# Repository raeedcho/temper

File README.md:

# temper

This is a split, wireless-only mechanical keyboard fashioned after the [chocofi keyboard](https://github.com/pashutk/chocofi). It started as a simple modification of the original chocofi PCBs to include battery pads and power switches for wireless use, but in the end, I thought there were enough changes to warrant giving it a separate designation. However, this design remains compatible with chocofi cases and plates.

## Features

- 36-key split keyboard with 3 rows x 5 columns + 3 thumb keys per half 
- Kailh choc spacing
- Sweep-like column stagger (with pinky columns 2 mm lower, like chocofi) with Corne-like thumb cluster
- Reversible PCB (so one design can be used for both halves)
- Kailh choc hotswap sockets
- Intended to be used with [nice!nano](https://nicekeyboards.com/nice-nano)
- Uses 7-pin SPDT power switch and includes pads for battery on keyboard shield PCB
- Support for [nice!view](https://nicekeyboards.com/nice-view)
- Compatible with chocofi cases and plates

## List of changes from original chocofi

- Add power switch
- Add solder pads for battery under ProMicro footprint
- Add footprint for a nice!view screen
- Switch out diode footprints for ones that have solder pads on both sides
- Switch ProMicro footprint for one that uses solder jumpers for cleaner design
- Remove TRRS jack
- Change reset switch out for one I could easily source from [Typeractive](https://www.typeractive.xyz)
- Rework KiCAD schematic for more pleasant development

## Bill of Materials

- 2x PCB (gerber files in [releases](https://github.com/raeedcho/temper/releases))
- 2x nice!nanos
- 2x LiPo batteries (see nice!nano documentation for suggestions)
- 2x Alps miniature SPDT switches
- 2x Panasonic miniature momentary button switches 
- 36x Kailh choc v1 switches
- 36x Kailh choc hotswap sockets
- 36x Choc v1 keycaps
- 36x 1N4148W SMD diodes
- (Technically optional but highly recommended) MCU socket:
  - 4x Mill-Max 310 series machine sockets
  - 48x Mill-Max pins for socketing microcontrollers
- (Optional) Minimal back plate case:
  - 2x 3mm acrylic back plate (SVG file for laser cutting in [case folder](case/temper-bottomplate.svg))
  - 10x M2 4 or 5mm brass standoffs (I used 5mm, but some users have said that 4mm fits better)
  - 20x M2 3mm screws
- (Optional) 2x FR-4 switch plate (goes well with the back plate--gerber files in [releases](https://github.com/raeedcho/temper/releases))
- (Optional) 2x nice!view screens

## Assembly

Assembly of this keyboard requires soldering the jumpers on the front-side of each PCB (underneath the microcontrollers). Past this, the assembly of this keyboard is similar to that of many other split wireless keyboards--there are many guides online to help. In case it helps with assembly, there's a screenshot of the PCB schematic in the somewhat incomplete [PCB folder readme](https://github.com/raeedcho/temper/tree/main/pcb).

Briefly, the full list of steps includes:

- Solder the jumpers underneath where the microcontrollers and battery would go (on PCB front). It's best to do this step first, since it's easiest when there are no other components on the board.

- On PCB back:
  - Solder the diodes (ensuring diodes are oriented correctly--check diode schematic to match orientation to PCB)
  - Solder the switch sockets
- On PCB front:
  - Solder reset switch
  - Solder power switch
  - [Socket microcontroller](https://docs.splitkb.com/hc/en-us/articles/360011263059-How-do-I-socket-a-microcontroller-):
    - Solder sockets into PCB
    - Place masking tape (to divert solder from socket for next soldering step)
    - Insert Mill-Max pins or diode legs
    - Place microcontroller (blank side up)
    - Solder pins to microcontroller
    - Carefully remove microcontroller
    - Remove tape
  - (optional) socket nice!view displays (same procedure as socketing microcontroller)
  - *Carefully* solder battery wires to pads (ensuring wires don't short together--I used masking tape to secure wires)
  - Reseat microcontroller
- Putting it all together (follow specific case instructions if applicable)
  - (optional) For back plate:
    - attach standoffs to PCB with screws
    - slide PCB standoffs into the aligned backplate holes
    - secure backplate in place with M2 screws (the backplate will be sandwiched in place between the hot swap sockets and the screw heads)
  - If not using switch plate:
    - press switches directly into PCB sockets (ensuring switch legs make it into the sockets and don't bend out of the way)
  - If using switch plate:
    - press switches into plate
    - align switches with PCB holes and press into sockets (ensuring legs make it into sockets and don't bend out of the way)
  - Place keycaps on switches

## Firmware

This keyboard uses [ZMK firmware](https://zmk.dev), which allows for configuration through GitHub Actions. An example configuration repository is [here](https://github.com/raeedcho/temper-zmk-config.git). The temper has also been added as an outboard on [Miryoku ZMK](https://github.com/manna-harbour/miryoku_zmk) via this [pull request](https://github.com/manna-harbour/miryoku_zmk/pull/42).

## Case options

The temper should be compatible with any case that works on the chocofi. The pictures above show a minimal case using only a laser-cut acrylic backplate (SVG design [here](case/temper-bottomplate.svg)), held on by M2 screws and brass standoffs. It's also possible to add an FR-4 switch plate (KiCAD design [here](case/top-plate)), which helps keep the switches stable in the hot-swap sockets.

Other options:
- The [temper gasket case](https://github.com/calerouxz/TemperKB-case), designed specifically for the temper by [calerouxz](https://github.com/calerouxz). The gasket case is more complex than the simple acrylic backplate and FR-4 switch plate, but has a more polished final look and feel.
- This [custom temper case](https://github.com/AdrianBonpin/zmk-temper), designed by [AdrianBonpin](https://github.com/AdrianBonpin). This repository also contains another example firmware configuration, with support for [ZMK Studio](https://zmk.dev/docs/features/studio).
- A [CNC metal case](https://github.com/CoenTurk/temper-metal), designed by [CoenTurk](https://github.com/CoenTurk). See https://github.com/raeedcho/temper/pull/18 for images.
- A [case with room for a big 600 mAh battery](https://github.com/vdztvboven-cpu/temper-case), designed by [kulderzipke](https://github.com/vdztvboven-cpu).

## Why "temper"?

Tempering is a finicky process that changes the structure of chocolate to make it more shiny, but doesn't really change the taste much.

Likewise, the changes I made to the chocofi didn't alter the original design much, but made some quality-of-life improvements for both development and my own personal aesthetics, at the cost of removing traditional wired operation and possibly making it more difficult to assemble, given the addition of many solder jumpers. 

## Resources

I adapted a few of the elements from these KiCAD libraries for use in this design:

- [chocofi](https://github.com/pashutk/chocofi) - The PCB switch layout came from the original chocofi design
- [kbd](https://github.com/foostan/kbd) - This library, by foostan, the designer of the popular Corne keyboard, provides useful schematic symbols and footprints
- [keyswitches.pretty](https://github.com/daprice/keyswitches.pretty) - library of switch footprints--especially useful for reversible PCBs.
- [swoop](https://github.com/jimmerricks/swoop) - Contains reversible PCB footprints for ProMicro pinout, OLED screens, and 7-pin power switches.

## Similar keyboards

There are many similar keyboards to this one and the chocofi, and I'm sure they've all taken inspiration from each other at one point or another. Here's a (surely incomplete) list:

- [Corne/crkbd](https://github.com/foostan/crkbd) - A popular column stagger, 42-key split keyboard with many variants
- [Cornish Zen](https://lowprokb.ca/collections/keyboards/products/corne-ish-zen) - A low-profile wireless redesign of the Corne with choc spacing, screens, and an aluminum case
- [Kyria](https://splitkb.com/collections/keyboard-kits/products/kyria-rev3-pcb-kit) - Another popular columns stagger, 50-key split keyboard, supporting rotary encoders. MX spacing only, but supports both MX and choc switches. More extreme column stagger on the pinky than the Corne. Large thumb cluster.
- [Ferris](https://github.com/pierrechevalier83/ferris) - Minimalistic 34-key split keyboard borrowing the pinky column stagger of the Kyria. MCU is soldered directly onto the board--not ProMicro pinout compatible.
- [Ferris Sweep](https://github.com/davidphilipbarr/Sweep) - Redesign of the Ferris for ProMicro MCU pinout, which also allows for a diodeless build. Many variations.
- [Swoop](https://github.com/jimmerricks/swoop) - Fork of the Ferris Sweep to add OLED screens and encoders
- [Urchin](https://github.com/duckyb/urchin) - Another fork of the Ferris Sweep to add support for nice!view screens, though with a traditional switch matrix and diodes.
- [Swept Corne](https://github.com/AYM1607/swept-crkbd) - A wireless-only mix between the Corne and Ferris Sweep--basically a choc-spaced Corne with the Kyria pinky stagger (or alternatively a choc-spaced Kyria with a Corne thumb cluster)
- [Phase](https://github.com/mjpauly/phase) - 42-key split keyboard--mix of the original Ferris and Corne.
- [Fifi](https://github.com/raychengy/fifi_split_keeb) - 36-key split keyboard. Basically an MX Ferris Sweep with a Corne thumb cluster
- [Chocofi](https://github.com/pashutk/chocofi) - Choc version of the Fifi. Stagger is like the Kyria and Ferris keyboards, but with the pinky column 2mm lower. The keyboard this repository was based on.
- [Roost](https://github.com/forrestbaer/roost) - Wireless-only Ferris Sweep with an extra thumb key per hand
- [TOTEM](https://github.com/GEIGEIGEIST/TOTEM) - 38 key split keyboard with Sweep-like column stagger. 3 thumb keys, like Corne, but also an extra pinky key. Also designed with finger splay for the ring and pinky fingers.
- [A. Dux](https://github.com/tapioki/cephalopoda/tree/main/Architeuthis%20dux) - 34-key split keyboard with aggressive column stagger and splay
- [KLOR](https://github.com/GEIGEIGEIST/KLOR) - Customizable split keyboard (via versatile break-off PCBs), with on-board MCU, encoders, and OLED screens

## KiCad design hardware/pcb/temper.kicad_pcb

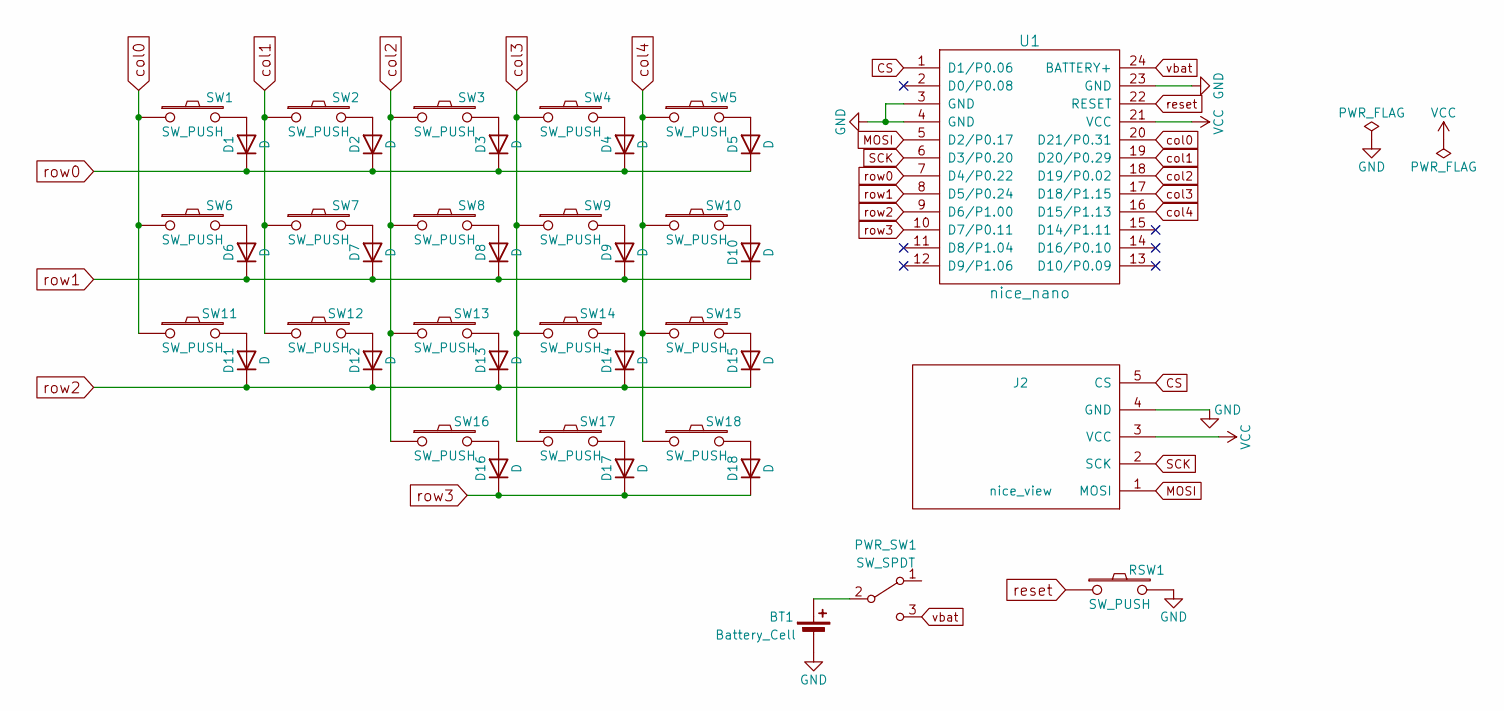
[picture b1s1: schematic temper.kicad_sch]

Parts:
BT1: Battery_Cell; Battery_pads_reversible
D1, D2, D3, D4, D5, D6, D7, D8, D9, D10, D11, D12, D13, D14, D15, D16, D17, D18: D; D_SMD_TH
J2: nice_view; nice_view_jumpers
PWR_SW1: SW_SPDT; power_switch_padreverse
RSW1: SW_PUSH; Panasonic_EVQPUL_EVQPUC_reversible
SW1, SW2, SW3, SW4, SW5, SW6, SW7, SW8, SW9, SW10, SW11, SW12, SW13, SW14, SW15, SW16, SW17, SW18: SW_PUSH; Kailh_socket_PG1350_reversible
U1: nice_nano; ProMicro_jumpers

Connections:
CS: J2.5 (CS), U1.1 (D1/P0.06)
GND: BT1.2 (-), J2.4 (GND), RSW1.2, U1.3 (GND), U1.4 (GND), U1.23 (GND)
MOSI: J2.1 (MOSI), U1.5 (D2/P0.17)
unnamed: BT1.1 (+), PWR_SW1.2 (B)
unnamed: D1.2 (A), SW1.2
unnamed: D2.2 (A), SW2.2
unnamed: D3.2 (A), SW3.2
unnamed: D4.2 (A), SW4.2
unnamed: D5.2 (A), SW5.2
unnamed: D6.2 (A), SW6.2
unnamed: D7.2 (A), SW7.2
unnamed: D8.2 (A), SW8.2
unnamed: D9.2 (A), SW9.2
unnamed: D10.2 (A), SW10.2
unnamed: D11.2 (A), SW11.2
unnamed: D12.2 (A), SW12.2
unnamed: D13.2 (A), SW13.2
unnamed: D14.2 (A), SW14.2
unnamed: D15.2 (A), SW15.2
unnamed: D16.2 (A), SW16.2
unnamed: D17.2 (A), SW17.2
unnamed: D18.2 (A), SW18.2
SCK: J2.2 (SCK), U1.6 (D3/P0.20)
VCC: J2.3 (VCC), U1.21 (VCC)
col0: SW1.1, SW6.1, SW11.1, U1.20 (D21/P0.31)
col1: SW2.1, SW7.1, SW12.1, U1.19 (D20/P0.29)
col2: SW3.1, SW8.1, SW13.1, SW16.1, U1.18 (D19/P0.02)
col3: SW4.1, SW9.1, SW14.1, SW17.1, U1.17 (D18/P1.15)
col4: SW5.1, SW10.1, SW15.1, SW18.1, U1.16 (D15/P1.13)
reset: RSW1.1, U1.22 (RESET)
row0: D1.1 (K), D2.1 (K), D3.1 (K), D4.1 (K), D5.1 (K), U1.7 (D4/P0.22)
row1: D6.1 (K), D7.1 (K), D8.1 (K), D9.1 (K), D10.1 (K), U1.8 (D5/P0.24)
row2: D11.1 (K), D12.1 (K), D13.1 (K), D14.1 (K), D15.1 (K), U1.9 (D6/P1.00)
row3: D16.1 (K), D17.1 (K), D18.1 (K), U1.10 (D7/P0.11)
vbat: PWR_SW1.3 (C), U1.24 (BATTERY+)

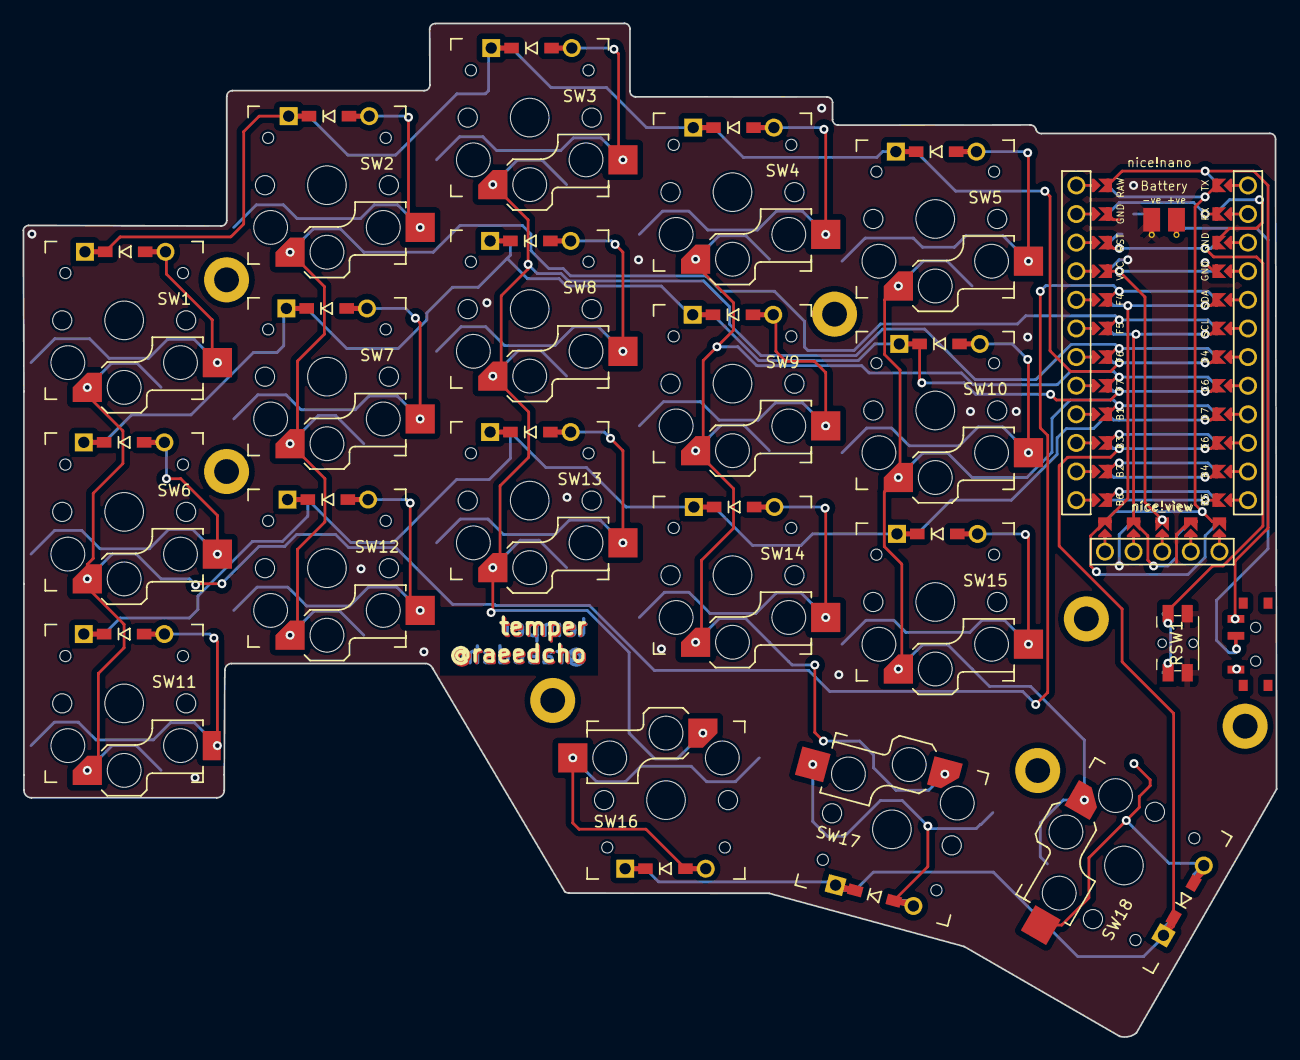
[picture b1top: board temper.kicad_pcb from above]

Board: 2 copper layers, 111.3 x 90.0 mm, 48 parts (0 on the bottom side), 35 nets.

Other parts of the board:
H1: h1; LEGO_HOLE
h2: h2; LEGO_HOLE
h3: h3; LEGO_HOLE
h4: h4; LEGO_HOLE
h5: h5; LEGO_HOLE
h6: h6; LEGO_HOLE
h7: h7; LEGO_HOLE

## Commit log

2023-07-07 feat: add gitignore
2023-07-07 feat: add kicad-specific gitignore
2023-07-07 feat: add kbd and keyswitches pcb libraries as submodules
2023-07-13 feat: add swoop footprint library
2023-07-13 feat: add specialized library for dumta keyboard
2023-07-13 feat: add dumta schematic, pcb, and other files
2023-07-13 feat: add JLCPCB design rules, as best I can tell
2023-07-13 feat: move some footprints over to dumta library
2023-07-13 feat: change footprints and alter them to match design rules
2023-07-13 fix: fix all major design rule errors
2023-07-13 chore: change design rule warning spec
2023-07-14 refactor: rename kicad project to temper, keeping the library name the same
2023-07-14 feat: change some output settings
2023-07-14 doc: add readme file
2023-07-14 Add CERN Open Hardware License
2023-07-14 fix: add nice!nano and nice!view silkscreen
2023-07-17 doc: add some info to readme
2023-07-17 doc: clean up readme a little bit
2023-08-25 doc: update readme with firmware info
2023-08-25 doc: update readme to remove a TODO
2023-09-06 feat: add bottomplate svg file
2023-09-06 refactor: move elements of hardware folder to root
2023-09-06 doc: add images to readme
2023-09-06 doc: Update README.md
2023-09-07 fix: remove duplicate plate from bottom plate SVG
2023-09-18 doc: Update README with info about Gerber releases
2023-09-18 doc: fix typo in README.md
2023-09-18 docs: add info about bottom plate SVG file
2023-09-18 doc: add items to BOM and add assembly instructions
2023-09-18 doc: fix typo in README
2024-01-08 doc: nice!view display confirmed working
2024-01-09 doc: update standoff info in readme
2024-01-15 feat: add STEP file for PCB (for designing cases)
2024-03-24 feat: add PCB schematic for top plate
2024-03-24 fix: save plate modification
2024-03-24 fix: add project file to gitignore (only need pcb file)
2024-04-13 doc: update readme with case and firmware options
    Update from calerouxz: https://github.com/raeedcho/temper/issues/11
2024-04-17 doc: clarify jumper location in README.md
    Clear up ambiguous language in assembly instructions related to which side to solder jumpers
2024-04-17 feat: remove useless holes from top plate
2024-04-17 doc: add information about switch plate
2024-05-01 Added full-case drawings and step-files
2024-05-01 Renamed folder
2024-10-30 docs: add soldered jumpers image
2024-10-31 feat: add a scale legend to the bottom plate svg
2024-12-23 doc: add PCB readme and schematic image
2024-12-23 doc: update README.md with link to PCB schematic
2025-05-19 Update README.md with new description of backplate assembly
    Attempt to reduce confusion about how the minimal backplate case assembly works.
2025-05-19 Update README.md with new backplate assembly description
    Remove some confusion on minimal backplate assembly description
2025-10-14 Update README.md with new case option
    Added link to a new user-created case option
2025-11-03 Add CNC metal case option to README
2026-06-25 small stylistic update to readme
2026-06-25 feat: add a contributed big-battery case option to readme (#33)
    * Update README.md
    * small stylistic update to readme
    ---------
